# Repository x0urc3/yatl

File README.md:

# [Work-in-Progress] Yet Another Temperature Logger
A coin cell powered precision temperature logger

# Development tools
1. [Kicad](https://www.kicad.org/)
2. [PlatformIO](https://platformio.org/)
3. Python/Bash

# Release
## Version 0.5
- Initial prototype
- ATMega48 microcontroller and LMT86 temperature sensor
- Temperature data is stored in the ATMega48 EEPROM. Sampled every 2 minutes for a duration of 8 hours

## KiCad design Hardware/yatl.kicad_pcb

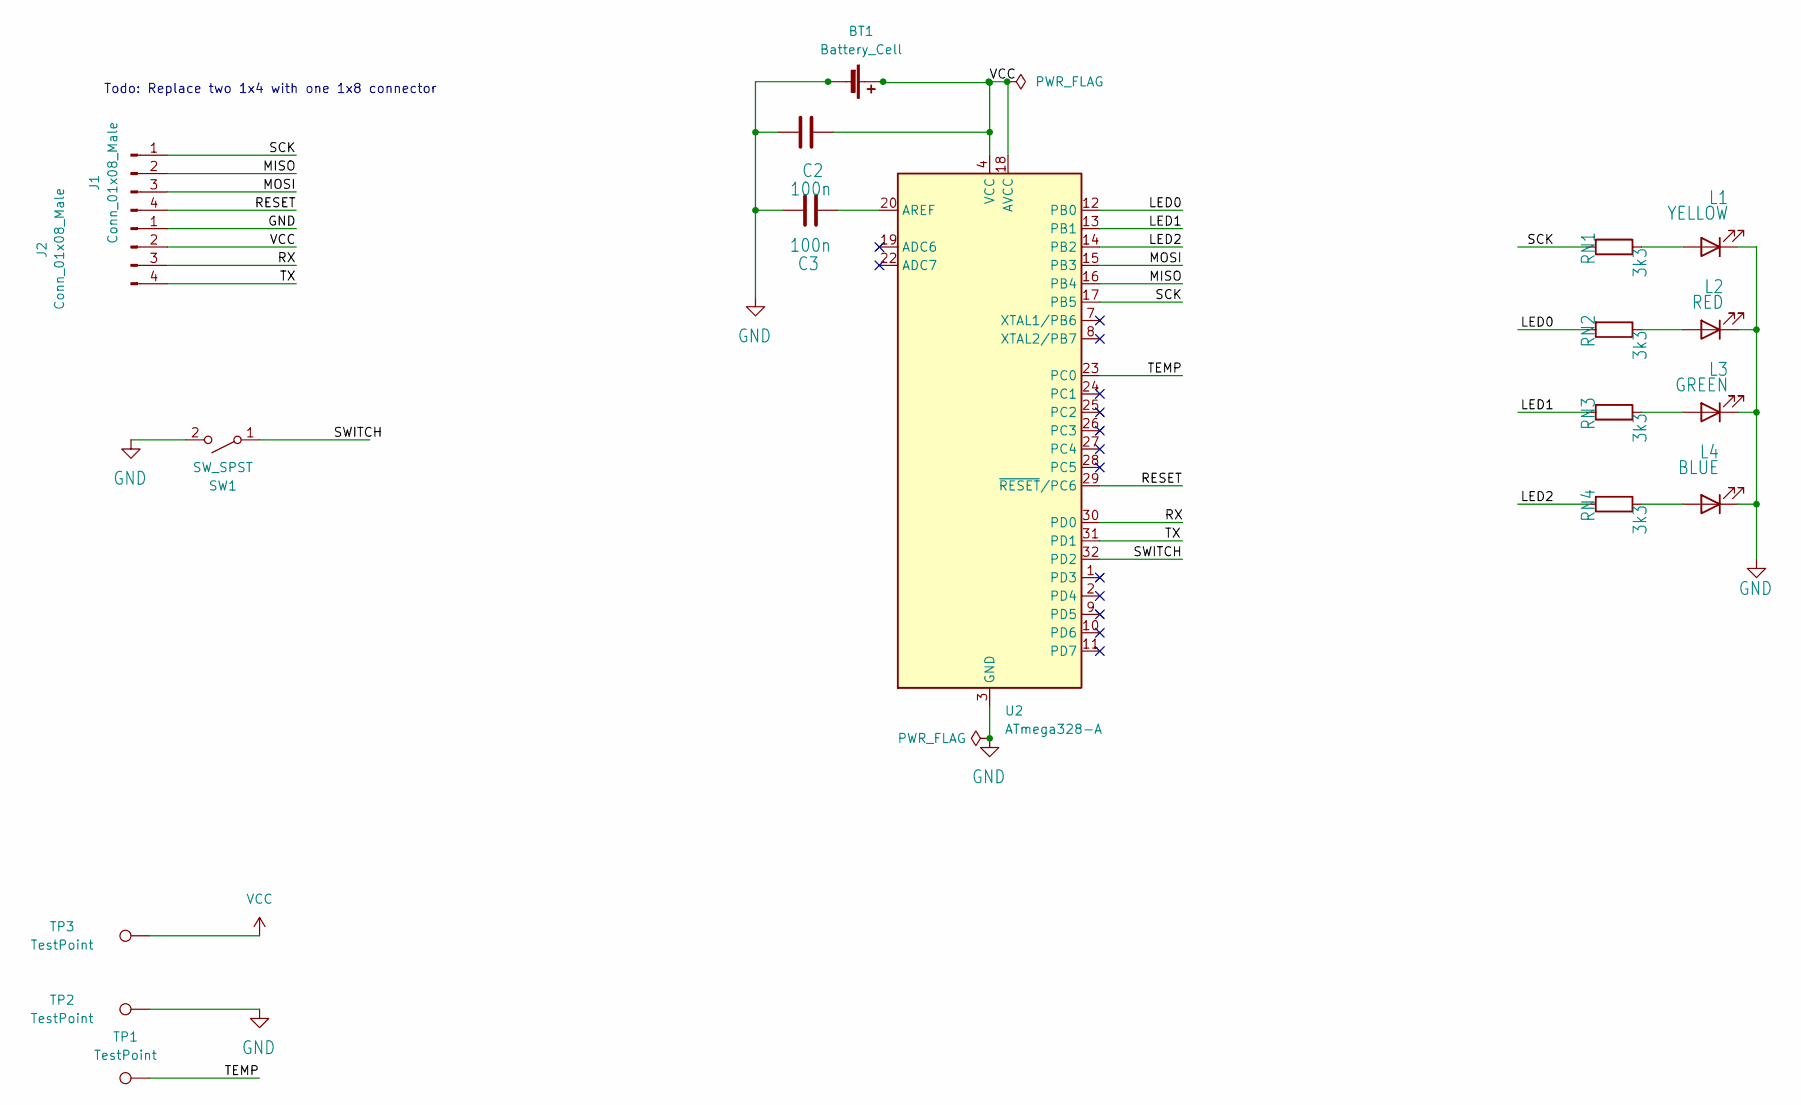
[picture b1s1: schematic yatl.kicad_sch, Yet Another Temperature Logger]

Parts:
BT1: Battery_Cell; BatteryHolder_Keystone_3034_1x20mm
C2, C3: 100n; C_1206_3216Metric_Pad1.33x1.80mm_HandSolder
J1, J2: Conn_01x08_Male; Testpoint_1x04_P2.54mm
L1: YELLOW; LED_1206_3216Metric_Pad1.42x1.75mm_HandSolder
L2: RED; LED_1206_3216Metric_Pad1.42x1.75mm_HandSolder
L3: GREEN; LED_1206_3216Metric_Pad1.42x1.75mm_HandSolder
L4: BLUE; LED_1206_3216Metric_Pad1.42x1.75mm_HandSolder
RN1, RN2, RN3, RN4: 3k3; R_1206_3216Metric_Pad1.30x1.75mm_HandSolder
SW1: SW_SPST; SW_Push_1P1T_NO_6x6mm_H9.5mm
TP1, TP2, TP3: TestPoint; TestPoint_Pad_3.0x3.0mm
U2: ATmega328-A; TQFP-32_7x7mm_P0.8mm

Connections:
/LED0: RN2.2, U2.12 (PB0)
/LED1: RN3.2, U2.13 (PB1)
/LED2: RN4.2, U2.14 (PB2)
/MISO: J1.2, U2.16 (PB4)
/MOSI: J1.3, U2.15 (PB3)
/RESET: J1.4, U2.29 (~RESET/PC6)
/RX: J2.3, U2.30 (PD0)
/SCK: J1.1, RN1.2, U2.17 (PB5)
/SWITCH: SW1.1 (A), U2.32 (PD2)
/TEMP: TP1.1, U2.23 (PC0)
/TX: J2.4, U2.31 (PD1)
GND: BT1.2 (-), C2.1, C3.2, J2.1, L1.1 (K), L2.1 (K), L3.1 (K), L4.1 (K), SW1.2 (B), TP2.1, U2.3 (GND), U2.5 (GND), U2.21 (GND)
unnamed: C3.1, U2.20 (AREF)
unnamed: L1.2 (A), RN1.1
unnamed: L2.2 (A), RN2.1
unnamed: L3.2 (A), RN3.1
unnamed: L4.2 (A), RN4.1
VCC: BT1.1 (+), C2.2, J2.2, TP3.1, U2.4 (VCC), U2.6 (VCC), U2.18 (AVCC)

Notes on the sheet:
Todo: Replace two 1x4 with one 1x8 connector

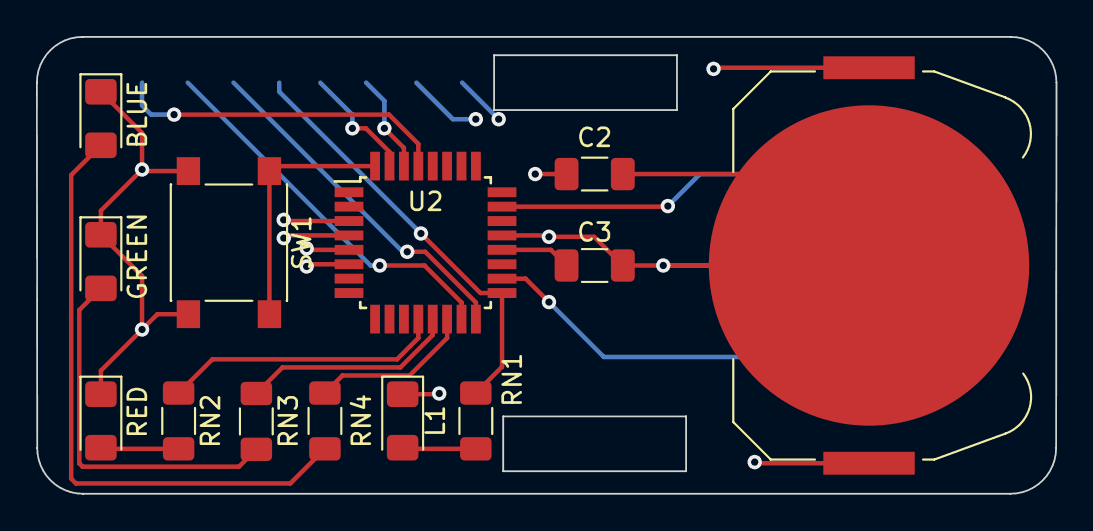
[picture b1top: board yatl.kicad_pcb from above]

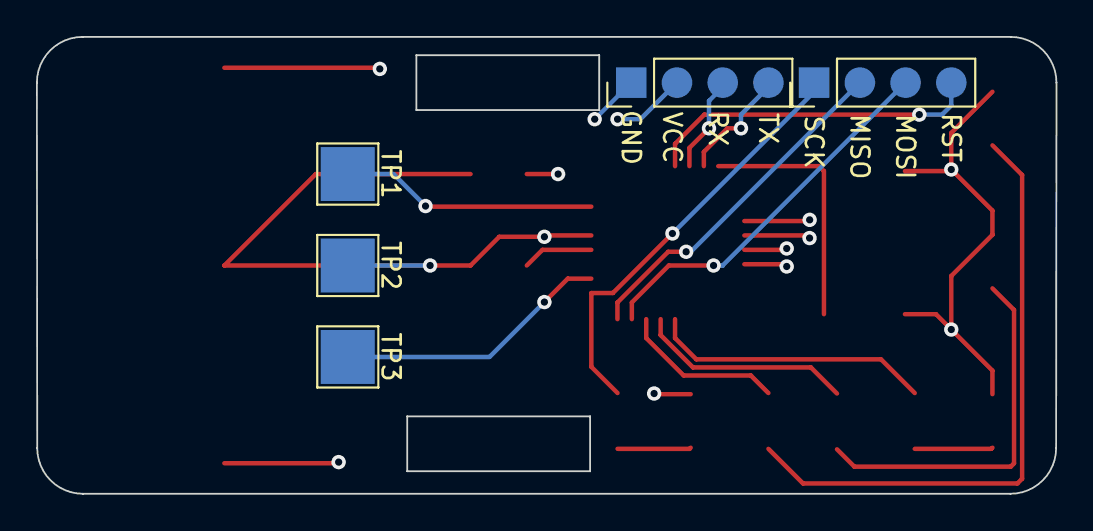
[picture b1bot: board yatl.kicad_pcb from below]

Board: 4 copper layers, 56.6 x 25.4 mm, 18 parts (5 on the bottom side), 18 nets.

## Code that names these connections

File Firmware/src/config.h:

/* config.h Copyright (c) 2022 Khairulmizam Samsudin <xource@gmail.com
 *
 * Pins and configuration declaration
 *
 */

#ifndef CONFIG_H_
#define CONFIG_H_

#include <avr/io.h>

// Reserved pins    ATMega | Phy |  Uno
// Reset             PC6   |  1  |   reset
// SCK               PB5   |  19 |   13
// MISO              PB4   |  18 |   12
// MOSI              PB3   |  17 |   11
// SDA               PC4   |  27 |   A4
// SCL               PC5   |  28 |   A5
// TX                PD1   |  2  |   1
// RX                PD0   |  3  |   0
// ARef (100nF Gnd)  ARef  |  20 |   ARef

// pinout         ATMega    | Phy  |  Uno
#define LED1        PB0   //       |  x     |  x
#define LED2        PB1   //       |  x     |  x
#define LED3        PB2   //       |  x     |  x
#define LEDDDR      DDRB
#define LEDPORT     PORTB
#define TEMPPIN     0xf0  //   23  |  A0
#define SWITCH      PD2   //       |  x     |  x
#define SWITCH_PIN  PIND
#define SWITCH_PORT PORTD
#define SWITCH_DEBOUNCE_TIME 100

#endif  // CONFIG_H_

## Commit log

2022-05-25 build: project setup
2022-05-25 Add function to read internal temperature sensor
2022-05-25 design: define reserved pins
2022-05-25 Add LMT86 temperature sensor function
2022-05-26 Add ADC prescaler for different board
2022-05-26 Fix calculation error
2022-05-26 BUG: Identified bug in getInternalTemp()
2022-05-26 debug: Added functions related to serial debugging
2022-05-26 Add getVCC100() to determine battery voltage
2022-05-26 Fix bug in getInternalTemp() when changing input channel - Add settling time after changing ADMUX - Add/increase settling time for other ADC related functions
2022-05-26 Refactor code to print one floating point
2022-05-26 build: Add target environment without Arduino framework
2022-05-28 Replace with safe verstion of sprintf()
2022-05-28 Initialize Kicad project and copied Arduino Uno microcontroller schematic
2022-05-31 Added schematic and update pins definition
2022-05-31 Route PCB and update schematics - Add 1x4 testpoint footprint in a project library - Replace LMT86 footprint with 3 1x1 test point - Fix battery decoupling capacitor wiring
2022-06-01 Restructure utility functions into library
2022-06-02 Rename library to avr_util
2022-06-02 Lump all utility function into ./src
2022-06-02 Add USART - Add rx/tx USART functionality - Rename debug.h to trace.h - Add USART feature to TRACE - Automatic detection of Arduino Serial library
2022-06-02 Move generic adc function to separate file
2022-06-02 Use getVcc100() to define adc vref
2022-06-03 Add configuration and fuses for target ATmega328p
2022-06-03 Add eeprom initialization
2022-06-04 Add sleep function
2022-06-04 Add code and configuration for ISP and monitor program
2022-06-04 Ignore ctags generated file
2022-06-04 Add switch definition and function
2022-06-04 Add timeout counter for timing user interaction
2022-06-04 Remove Arduino framework dependencies
2022-06-04 Remove Arduino framework dependencies and use function-like macro
2022-06-05 Code cleanup - Lineup comment - Added static to function definition - Remove unnecessary comment
2022-06-05 Enhance tracer.h - Add different verbosity level to TRACER macro - TRACERVERBOSE default to 1 - renamed enabler flag to TRACER
2022-06-05 Change logic soo that smaller verbosity level will be printed
2022-06-06 Ignore vimrc configuration file
2022-06-06 Fix bug due to location of variable declaration
2022-06-06 Add sleep state and PCINT for wakeup
2022-06-06 Power down mode disable ALL clock and oscillator
2022-06-06 Add UI state
2022-06-06 Rename EEPROM variables
2022-06-06 Add and track different UI state
2022-06-06 Fix bug reading rom storage size and rename macro variable
2022-06-06 Move tracer initialization before setup()
2022-06-06 Rollover the UI counter
2022-06-06 Add state variable for use in each loop and use currentState across loop
2022-06-06 Restructure UI state
2022-06-07 Fix sleep state bug and remove unused variable
2022-06-07 Add WDT for logging
2022-06-07 Remove warning messages by #warning and unused function
2022-06-07 Perform logging everytime WDT expire and logging enabled
2022-06-07 Add cpplint configuration file
2022-06-07 Change the root dir for cpplint
2022-06-07 Code cleanup and linting
2022-06-08 Rename variable
2022-06-08 Log based on predefined interval and EEPROM size
2022-06-09 Separate env for develop and debug - develop enable TRACE - debug enable symbolic debug info for gdb
2022-06-09 Implement eeprom storage
2022-06-09 Create EEPROM storage data struct and implement usageEEPROM()
2022-06-09 Ignore data directory
2022-06-09 Add bash script to dump and clear EEPROM
2022-06-09 Use standard return 0 for success
2022-06-09 Add arguments and cleanup
2022-06-09 Rename script
2022-06-09 Skeleton code
2022-06-09 Use update to reduce possibility of writing to EEPROM
2022-06-09 Add script to convert Intel Hex to csv
2022-06-09 Add option for avrdude terminal
2022-06-16 Fix DIRTYFLAG size
2022-06-16 Fix for storing byte data using word-based addressing
2022-06-16 Clear word size dirty flag
2022-06-16 Add copyright notice
2022-06-16 Remove ISP and monitor code
2022-07-01 Fix pitch between connectors
2022-07-02 Move pins and configurations to config.h
2022-07-02 Move getTem10() to adc.h
2022-07-02 Add ISP and monitor program
2022-07-02 Test all LED
2022-07-02 Add new source file to test board functionality
2022-07-02 Add interrupt switch to flip direction of LED shifting
2022-07-02 Use config.h for pins and configuration declaration
2022-07-02 Add temperature sensing
2022-07-02 Create setup()
2022-07-03 Change LED resistor to 2k
2022-07-03 Rename LED and reposition connector label
2022-07-03 ATMega48 is for environment release & board. ATMega328 for dev and debug
2022-07-03 Add doBlinkLED() after timer expired to confirm state selection
2022-07-03 Add doStatusLED() to change status indicator
2022-07-03 Add maxEEPROM() to provide maximum EEPROM size
2022-07-03 Add showResultLED() to indicate battery and storage value using LED
2022-07-03 Fix delay unit
2022-07-03 Update fuse flag for ATmega48
2022-07-03 Multiple enhancement - Add argument to upload ArduinoISP - Add variable to define AVR part id for avrdude - Dump eeprom to stdout
2022-07-03 Update fuse for ATMega328P and ATMega48
2022-07-04 Add custom unity unittest configuration to use AVR serial
2022-07-04 Enable arduino framework to use native Arduino test
2022-07-04 Add test for switching on led
2022-07-05 Increase LED resistor value to reduce current consumption
2022-07-05 Remove LMT86 decoupling capacitor that cause sudden temperature spike after certain minutes
2022-07-05 Add LED indicator when logging started
2022-07-05 Update README for v0.5 release
2022-07-06 Call getVcc100() earlier to ensure ADC settles down
2022-07-07 Add function to repeat ADC conversion after changing voltage reference
2022-07-07 Split TRACE into smaller unit
2022-07-07 Fix Watchdog WDIE initialization failure
2022-07-07 Add test initWDT() for
2022-07-07 Add TRACE
2022-07-14 Add monitor mode
2022-07-14 Add software serial configuration
2022-07-14 Fix software serial baud rate
2022-07-19 Migrate build system to CMake. Toolchain definition is provided by avr-gnu.cmake
2022-07-19 Ignore vim swap files
2022-07-19 Undefine TRACER when NDEBUG is defined
2022-07-22 Replace deprecated ADDITIONAL_MAKE_CLEAN_FILES and reduce avrdude verbosity
2022-07-22 Create directory for cmake scripts
2022-07-22 Move custom target to a new add_avr_target()
